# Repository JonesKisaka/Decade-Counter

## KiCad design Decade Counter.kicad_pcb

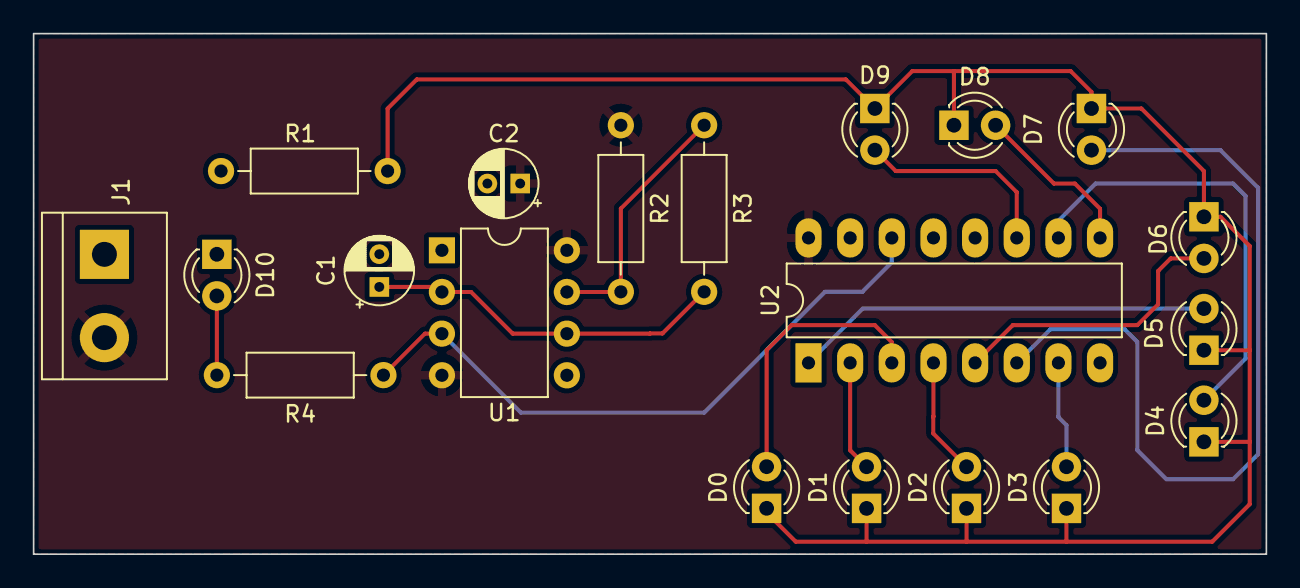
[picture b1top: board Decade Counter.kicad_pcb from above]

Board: 2 copper layers, 75.2 x 31.8 mm, 20 parts (0 on the bottom side), 17 nets.

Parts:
C1, C2: 1uF; CP_Radial_D4.0mm_P2.00mm
D0, D1, D2, D3, D4, D5, D6, D7, D8, D9, D10: LED; LED_D3.0mm_Clear
J1: Screw_Terminal_01x02; TerminalBlock_bornier-2_P5.08mm
R1, R4: 330; R_Axial_DIN0207_L6.3mm_D2.5mm_P10.16mm_Horizontal
R2: 1k; R_Axial_DIN0207_L6.3mm_D2.5mm_P10.16mm_Horizontal
R3: 100k; R_Axial_DIN0207_L6.3mm_D2.5mm_P10.16mm_Horizontal
U1: LM555xN; DIP-8_W7.62mm
U2: 4017; DIP-16_W7.62mm_LongPads

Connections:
6,2: C1.1, R3.2, U1.2 (TR), U1.6 (THR)
GND: C1.2, C2.2, D10.1 (K), J1.1, R1.2, U1.1 (GND), U2.8 (VSS), U2.13 (CKEN), U2.15 (Reset)
unnamed: D0.1 (K), D1.1 (K), D2.1 (K), D3.1 (K), D4.1 (K), D5.1 (K), D6.1 (K), D7.1 (K), D8.1 (K), D9.1 (K), R1.1
unnamed: D0.2 (A), U2.3 (Q0)
unnamed: D1.2 (A), U2.2 (Q1)
unnamed: D2.2 (A), U2.4 (Q2)
unnamed: D3.2 (A), U2.7 (Q3)
unnamed: D4.2 (A), U2.10 (Q4)
unnamed: D5.2 (A), U2.1 (Q5)
unnamed: D6.2 (A), U2.5 (Q6)
unnamed: D7.2 (A), U2.6 (Q7)
unnamed: D8.2 (A), U2.9 (Q8)
unnamed: D9.2 (A), U2.11 (Q9)
unnamed: D10.2 (A), R4.2
unnamed: R2.2, R3.1, U1.7 (DIS)
unnamed: R4.1, U1.3 (Q), U2.14 (CLK)
Vcc: C2.1, J1.2, R2.1, U1.4 (R), U1.8 (VCC), U2.16 (VDD)

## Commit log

2022-09-21 Add files via upload
    From the previous Clock Circuit or Timer using NE555, I have used it to generate a clock pulse for the Decade Counter.
